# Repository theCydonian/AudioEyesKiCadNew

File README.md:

# AudioEyesKiCadNew
PCB Files for AudioEyes

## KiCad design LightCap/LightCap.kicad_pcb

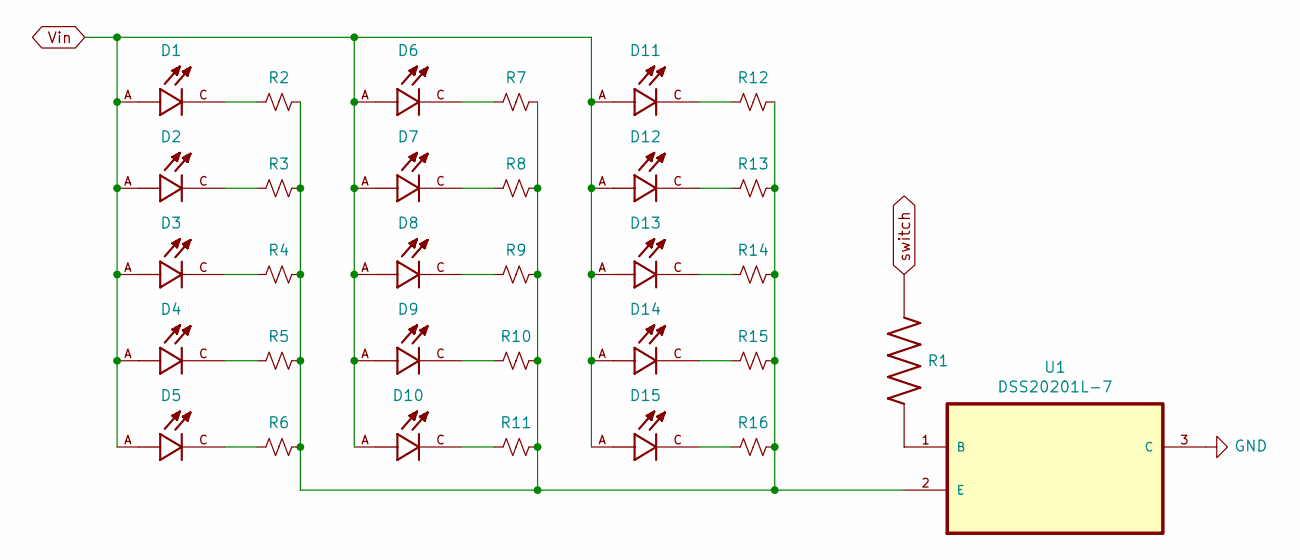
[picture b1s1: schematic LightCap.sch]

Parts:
D1, D2, D3, D4, D5, D6, D7, D8, D9, D10, D11, D12, D13, D14, D15: SPMWHT541ML5XATMS6; LED_SPMWHT541MP5WAPKS4; PARTREV 8.3
R1: ERJ-3EKF3000V; RESC1608X55N
R2, R3, R4, R5, R6, R7, R8, R9, R10, R11, R12, R13, R14, R15, R16: ERJ-PA2F36R0X; R_1206_3216Metric
U1: DSS20201L-7; SOT95P240X110-3N; MPN DSS20201L-7

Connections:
GND: U1.3 (C); also elsewhere on the board
unnamed: D1.C, R2.1
unnamed: D2.C, R3.1
unnamed: D3.C, R4.1
unnamed: D4.C, R5.1
unnamed: D5.C, R6.1
unnamed: D6.C, R7.1
unnamed: D7.C, R8.1
unnamed: D8.C, R9.1
unnamed: D9.C, R10.1
unnamed: D10.C, R11.1
unnamed: D11.C, R12.1
unnamed: D12.C, R13.1
unnamed: D13.C, R14.1
unnamed: D14.C, R15.1
unnamed: D15.C, R16.1
unnamed: R1.2, U1.1 (B)
unnamed 17: R2.2, R3.2, R4.2, R5.2, R6.2, R7.2, R8.2, R9.2, R10.2, R11.2, R12.2, R13.2, R14.2, R15.2, R16.2, U1.2 (E); also elsewhere on the board
Vin: D1.A, D2.A, D3.A, D4.A, D5.A, D6.A, D7.A, D8.A, D9.A, D10.A, D11.A, D12.A, D13.A, D14.A, D15.A
switch: R1.1

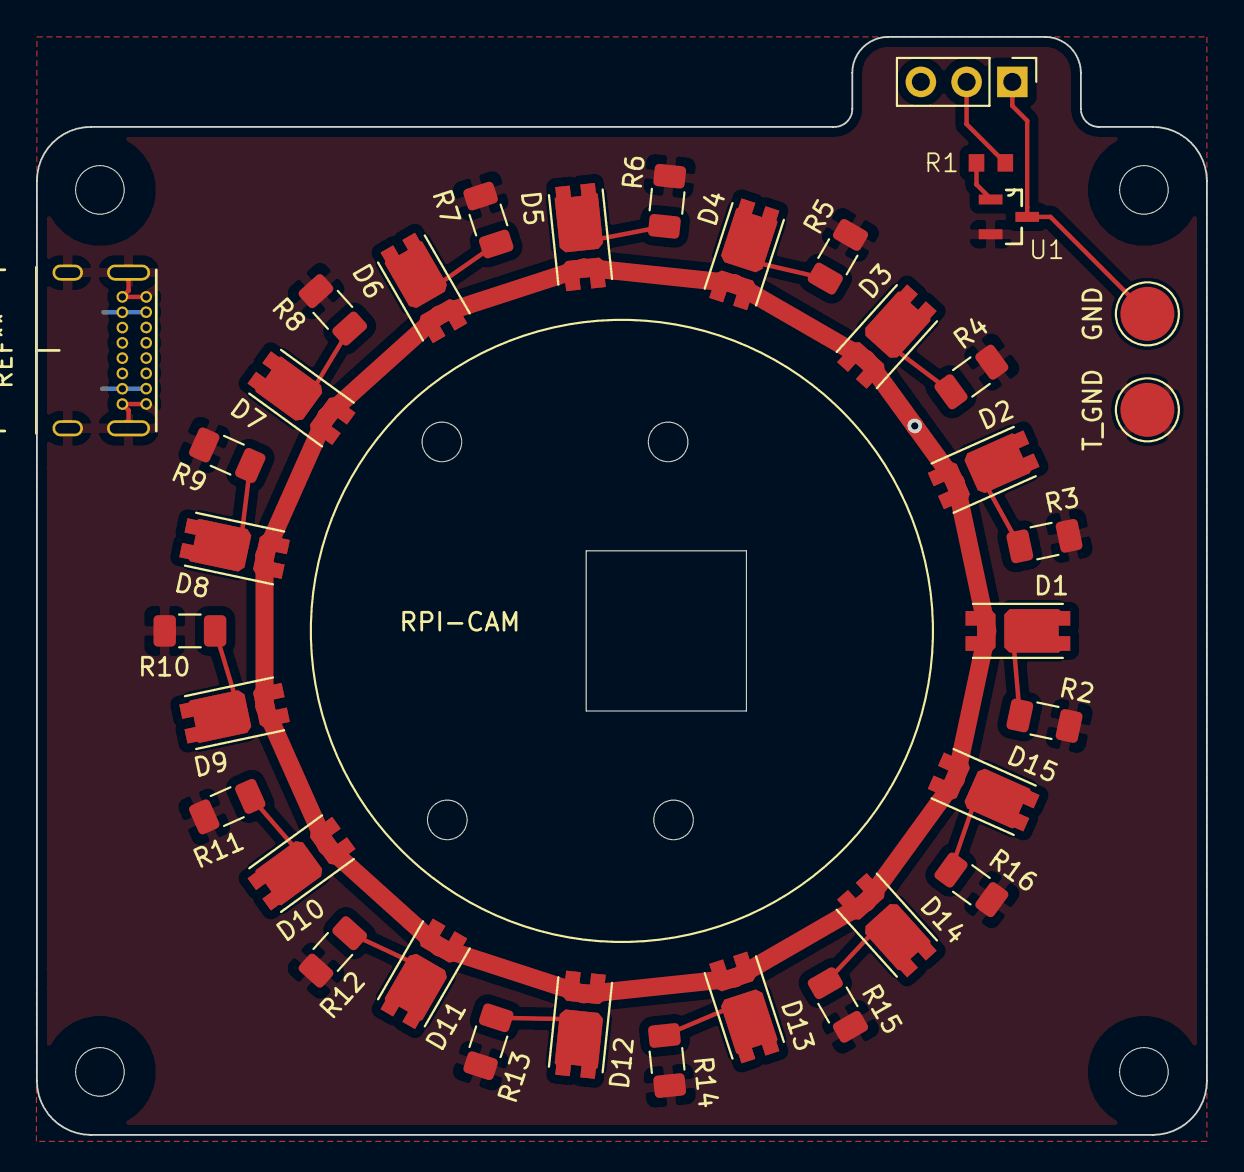
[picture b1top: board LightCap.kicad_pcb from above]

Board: 2 copper layers, 65.0 x 61.0 mm, 34 parts (0 on the bottom side), 19 nets.

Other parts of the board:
GND: TestPoint_Pad_D3.0mm
T_GND: TestPoint_Pad_D3.0mm

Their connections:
GND: GND.1; also elsewhere on the board
unnamed 17: T_GND.1; also elsewhere on the board

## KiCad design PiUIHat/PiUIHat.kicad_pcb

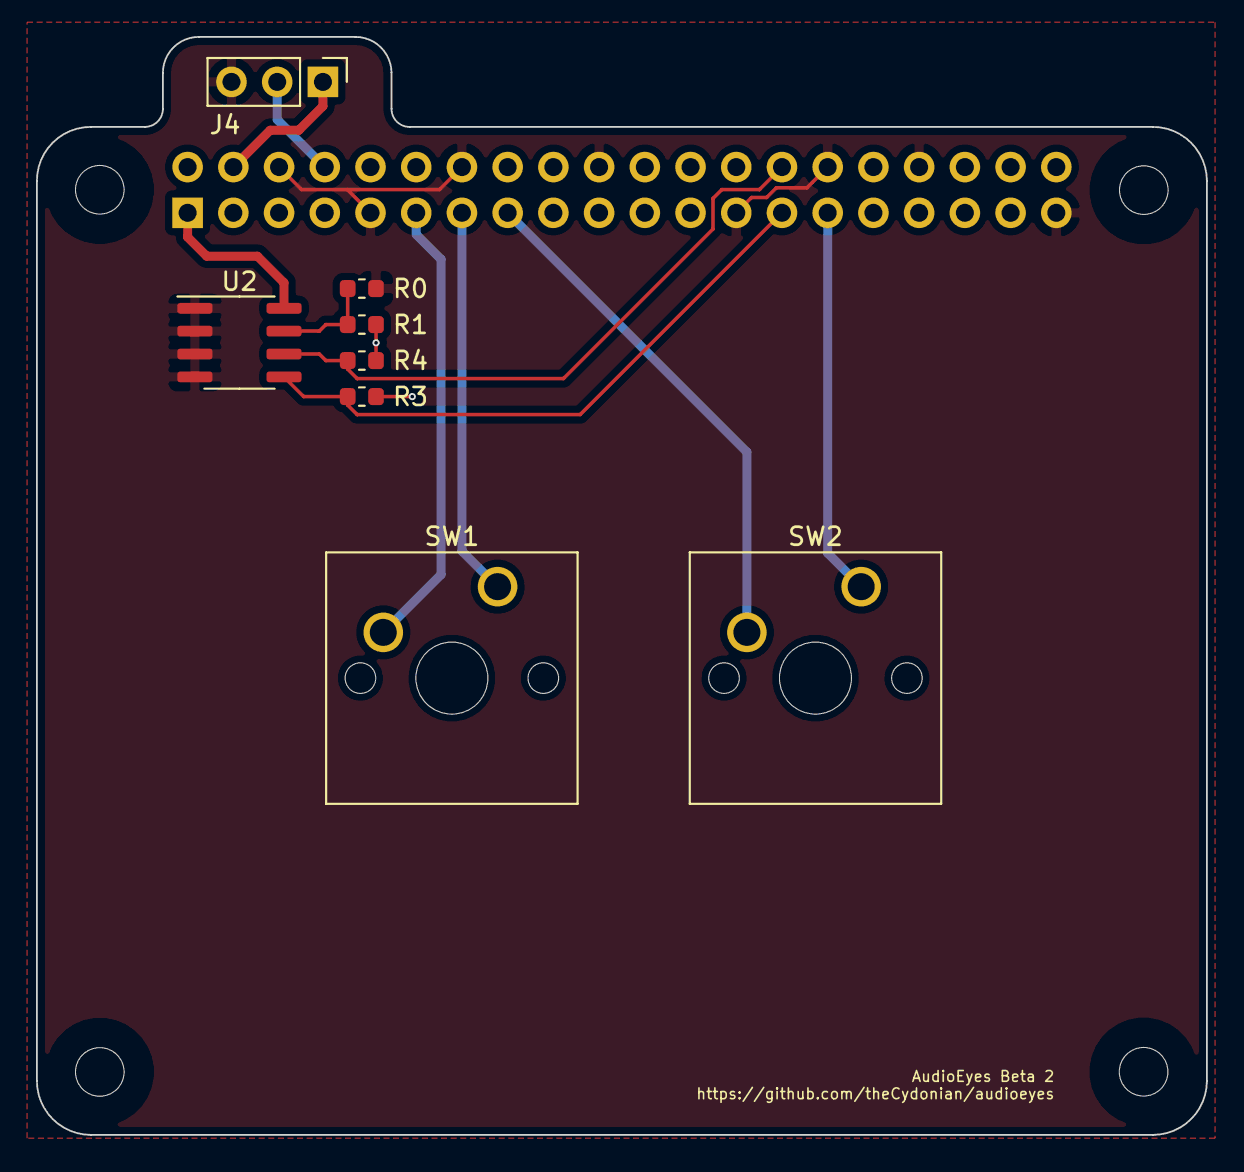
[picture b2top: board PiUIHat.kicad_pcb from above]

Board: 2 copper layers, 65.0 x 61.0 mm, 9 parts (1 on the bottom side), 11 nets.

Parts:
J3: 40HAT; PinSocket_2x20_P2.54mm_Vertical
J4: 3pin; PinHeader_1x03_P2.54mm_Vertical
R0: DNP; R_0603_1608Metric
R1: 10K; R_0603_1608Metric
R3, R4: 3.9K; R_0603_1608Metric
SW1, SW2: SW_Push; SW_Cherry_MX_1.00u_PCB
U2: CAT24C32; SOIC-8_3.9x4.9mm_P1.27mm

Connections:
/ID_SC_EEPROM: J3.28, R4.2, U2.6
/ID_SD_EEPROM: J3.27, R3.2, U2.5
/P3V3_HAT: J3.1, R1.1, R3.1, R4.1, U2.8
/P5V_HAT: J3.2, J3.4, J4.1
GND: J3.6, J3.9, J3.14, J3.20, J3.25, J3.30, J3.34, J3.39, J4.3, R0.2, U2.1, U2.2, U2.3, U2.4
unnamed: R0.1, R1.2, U2.7
in1: J3.13, SW1.1
in2: J3.29, SW2.1
out1: J3.11, SW1.2
out2: J3.15, SW2.2
switch: J3.8, J4.2

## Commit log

2022-03-28 whatever
2022-03-28 Added to README

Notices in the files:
parts and their libraries:
Copyright 2016 Accelerated Designs. All rights reserved.
